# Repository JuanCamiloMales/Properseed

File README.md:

# Properseed
 
## About
Our project focuses on the agricultural sector and aims to contribute to the solution of some challenges in this area. In this context, we identified several pain points that our solution can help solve, such as low crop productivity due to lack of optimization in the use of available resources and inefficient farming practices, which also leads to low profitability for farmers, lack of automation of farming operations (such as irrigation) and lack of data availability to improve knowledge-based decision making. Technology can contribute to improving these conditions, however, in the context of agriculture in our region, its adoption can be a challenge, especially for small producers, so our solution takes this situation into account by offering a product that is easy to use and implement at an affordable cost. 

## Features
The main functionality of our solution is the collection, management, and storage of crop weather data. This data is useful for the improvement of agricultural practices, such as the generation of early warnings, better pest management and crop control automation. We used Huawei Cloud resources to develop a solution that includes: 

- An IoT device for crop monitoring
- A crop yield prediction system based on historical data
- Extreme weather alerts on crops
- A web application for accessing device information, alerts and graphs
- A farmer assistance IVR

## Content
- Modelo3D: Device 3D model.
- PCB: Device circuit diagram.
- PaginaWeb: A React web application to access device data.
- arduino-app: Device program code.
- mqtt-app: Communication between device and storage.

## Authors
- Daniela Valencia Mellizo
- Andrés Felipe Jojoa
- Juan Camilo Males
- Javier Mauricio Fernández

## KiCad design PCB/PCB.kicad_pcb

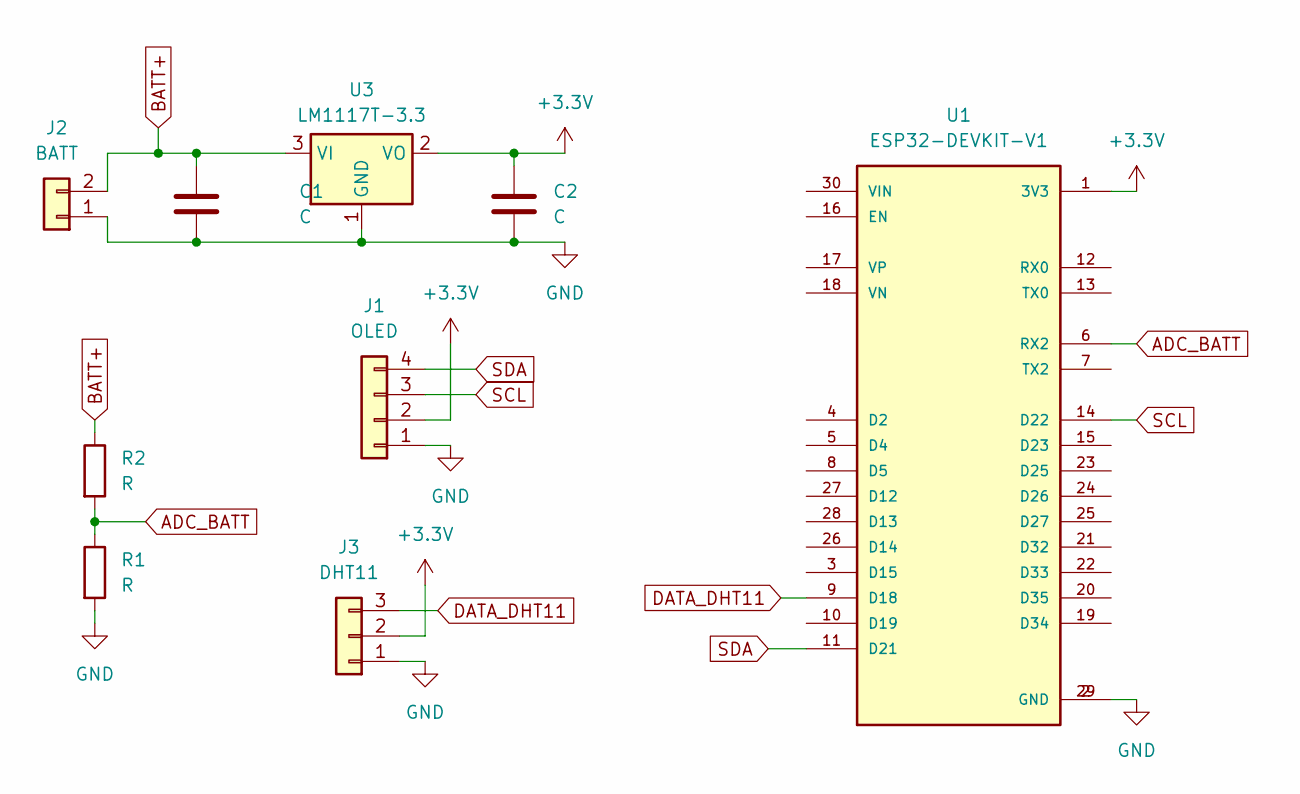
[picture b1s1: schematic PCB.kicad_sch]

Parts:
C1, C2: C; CP_Radial_D5.0mm_P2.50mm
J1: OLED; PinHeader_1x04_P2.54mm_Vertical
J2: BATT; JST_XH_B2B-XH-A_1x02_P2.50mm_Vertical
J3: DHT11; PinHeader_1x03_P2.54mm_Vertical
R1, R2: R; R_Axial_DIN0309_L9.0mm_D3.2mm_P15.24mm_Horizontal
U1: ESP32-DEVKIT-V1; MODULE_ESP32_DEVKIT_V1; PARTREV N/A
U3: LM1117T-3.3; TO-220-3_Horizontal_TabDown

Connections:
+3.3V: C2.1, J1.2, J3.2, U1.1 (3V3), U3.2 (VO)
ADC_BATT: R1.1, R2.2, U1.6 (RX2)
BATT+: C1.1, J2.2, R2.1, U3.3 (VI)
DATA_DHT11: J3.3, U1.9 (D18)
GND: C1.2, C2.2, J1.1, J2.1, J3.1, R1.2, U1.2 (GND), U1.29 (GND), U3.1 (GND)
SCL: J1.3, U1.14 (D22)
SDA: J1.4, U1.11 (D21)

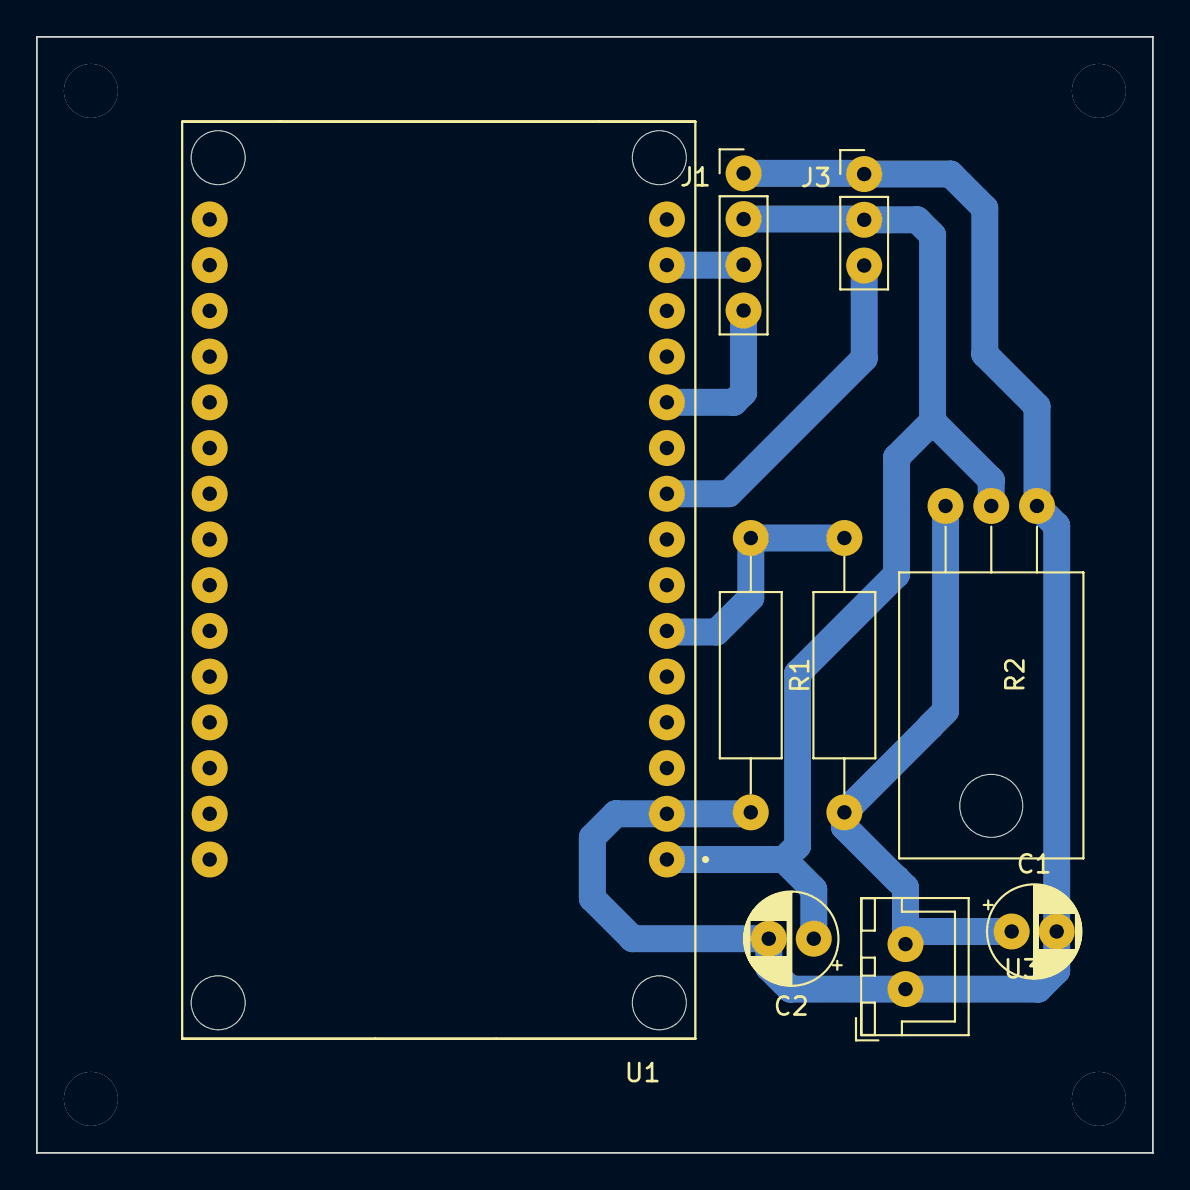
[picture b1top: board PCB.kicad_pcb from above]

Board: 2 copper layers, 62.0 x 62.0 mm, 9 parts (0 on the bottom side), 7 nets.

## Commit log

2023-11-18 Inicializacion Repositorio
2023-11-18 Ruta Home y Dispositivos
2023-11-20 Mapa y Dispositivos
2023-11-20 Agregar aplicacion mqtt Arduino
2023-11-20 Agregar Fecha hora libreria
2023-11-20 Agregar conexion mqtt libreria
2023-11-20 Correccion tiempo arduino mqtt
2023-11-20 Correccion agujeros PCB
2023-11-20 Elimina funciones innecesarias
2023-11-21 corrige formato de fecha
2023-11-22 Modelo3D
2023-11-22 Notificaciones
2023-11-22 Creación de cliente MQTT
2023-11-25 Charts and list devices
2023-11-25 Corrige ruta imagenes
2023-11-25 Correccion imagenes
